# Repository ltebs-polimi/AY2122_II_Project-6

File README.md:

# Project 6: Respiration Monitoring in Sleep Positions

# Contents
[Introduction](#introduction)

[Hardware](#hardware)

[Firmware](#firmware)

[Data acquisition](#data-acquisition)

[Signal processing](#signal-processing)

[Machine learning model](#machine-learning-model)

[Repository structure](#repository-structure)

##

## Introduction
The aim of the project is to develop a system able to correctly classify four different sleep positions using an accelerometer. From the accelerometer we had to extract information about the respiration rate and, from these data, perform a classification with different machine learning algorithms.  

The steps of the project will be: 

- Development of a wearable device, where the accelerometer will be positioned on the chest of the subject;
- Data acquisition: following the specific protocol;
- Data processing (filtering and extraction of respiratory rate);
- Development of a Machine Learning algorithm to correctly classify the position of a subject from the signal. 

## Hardware
The components used to perform this project are: 

- PSoC
- 3-axis accelerometer (LIS3DH)
- Bluetooth module (HC-06)
- LEDs (red and blue)
- 9V battery
- Switch
- Voltage regulator (LM340T5)

To create the hardware of the system we first realized it on a breadboard and used the connections to design the printed circuit board (PCB). 

To do so, we realized the schematic and the board design on eagle, selecting the correct components to be used. Once the PCB design was done, we were able to produce the physical board with a process of acid etching, on which we soldered all the components. 

The switch allows to turn on and off the system without removing the battery. Initially there were a voltage divider to reduce the input voltage from 9V to 5V but was replaced with the voltage regulator due to the Bluetooth module not turning on.

To contain the PCB we designed in Solidworks a case which was then 3D printed. The initial idea was to apply the case to the chest of the subject to acquire the data, but this idea was then discarded due to the high encumbrance of the case.

The hardware is subdivided into two main parts: PCB and accelerometer. The PCB contain all the physical elements and their connections, while the accelerometer is stitched on a strap and is connected to the PCB through long cables. 

In this way, we apply the strap on the thorax of the subject, reducing the encumbrance and allowing a free movement of the accelerometer, and the case is kept near the acquisition site.

## Firmware
The accelerometer and the microprocessor communicate with a I2C Master/slave communication and the data are sent with a Bluetooth module. Then, there are two digital output to drive two LED. The first one (blue) turns ON when the accelerometer is sampling, the second one (red) turns ON if some error occurs in the communication with the accelerometer. 

When the device turns on, the microprocessor reads and writes the registers of the accelerometer.
We set the sampling frequency (CTRL\_REG1) at 50 Hz, the Full Scale Range (CTRL\_REG4) at +-2g and we enable the FIFO mode.   

The device is in the “waiting” status in which the accelerometer is not sampling and the FIFO register is empty. 

When the user sends a “start” signal, the device starts sampling for three minutes (according to the protocol for collecting the data), the blue light turns on and the data is saved in the FIFO register. 
When the register is full, we send the data with the Bluetooth module and reset the FIFO register. After three minutes the procedures stops and the device returns in the “waiting” status. 

If an error occurs during the sampling procedure, the sampling stops and the red LED turns on. It is possible to stop the sampling even with a “stop” signal. 

## Data acquisition
The protocol for the data acquisition consists in collecting data of 10 people in 4 different positions (supine, prone, lateral left, lateral right). Each subject must keep the position for 3 minutes. 

To make the procedure easier we implement a graphical interface in which the user can communicate with the device. 

The user has to choose a port and connect to it. The application allows also to rescan the port or disconnect to the port if needed. 

Then the user has to choose the position of the subject and starts the sampling. It is possible also to stop the sampling. 

After three minutes the data is saved as ‘.csv’ in a specific folder. The data are automatically saved and labelled and every sampling has its own file. It is possible to change the position of the subjects and start another sampling. 

The ‘.csv’ file contains all the data of the three axis and the position of the subject. These files will be then processed to obtain the information about the respiratory signal. 

## Signal processing

### Introduction
In order to process the data to extract the respiration signal and consequently the reparation rate, we have tried two different approaches, both based on data normalization and filtering data with Moving-average and Butterworth filters.

The main difference between these two methods regards the computation of the respiration rate:

- The first one compute the respiration rate based on pick coating function;
- The second one compute the respiration rate based on fast Fourier transform.

We decided to adopt the second approach, based on literature reviews.

### Explanation of the principal steps
The following are the main steps used in the algorithm:

1.  Z-TRANSFORM AND WINDOWING

In order to smooth and compare the data, a Z-normalization is applied. Based on a preliminary analysis of the raw-data plot, we choose only the horizontal component (X,Y axis) of the acceleration to extract the respiration signal, because the Z axis is most influenced by the tone sound vibration of the heart. 

Looking to the final aim of the ML analysis, we decide to divide any posture registration of 3 minutes in 3 windows of 60 seconds. In this way, from any registration of each posture, we obtain 3 signals of one minutes enlarging the dataset having 12 signals for each recorded volunteer (instead of 4).

The further analysis is applied to a 60 second window.

2. FILTERING

We have filtered transformed raw-data in 60 seconds window applying a cascade of filter:

- Moving-Average Filtering: to reduce the noise, we have applied a Moving average filter on a window of length corresponding to a maximal breathing rate (40 breaths/min).

|Average window size |(40/60) x Sampling Frequencies |
| :- | :- |

- Butterworth Filtering: the respiration frequencies in physiological condition can vary from 8 to 40 breaths for minutes (0.13-0.66 HZ). Therefore to extract the respiration signal we need to enhance this range of frequencies applying a Butterworth filter with parameters that are reported in the table. 

|FILTER ORDER|LOW F. (Hz)|HIGH F. (Hz)|
| :-: | :-: | :-: |
|4|0.05|0.66|

- BR selection: from the filtered signal we compute the Fast Fourier transform in order to make a frequency analysis. Subsequently, computing its power spectrum it is possible to select the breathing rate looking at the range of frequencies corresponding to physiological one (8-40 breath/min). This corresponds to the maximal in that range.

### Time and frequencies index extraction
In order to make further analysis on the signal, especially the classification purpose, we create a final dataset in which we report different time and frequencies domain index computed on the signal. (The list of index are reported in "index_computation.pdf" file, inside the "Data_collection" folder) 

After computed the principal index for ML analysis  reported in the table, we merge all the created dataset to proceed further.

## Machine learning model
For the classification we explored different ways. 

First, we tried to classify with the raw data coming from the accelerometer, we reached an accuracy of 100% mainly because of the orientation of the gravity acceleration that gives the major contribute to the signal.  

Once we have extracted the respiratory signal we tried to perform a multi-classification in two different ways:
- Using the entire respiratory signal, but this strategy did not perform very well, returning an accuracy of 35%. Analyzing the confusion matrix was evident that the relative positions were almos all misclassified;
- Using time and frequency indexes

### Data preparation
1. Univariate analysis: we removed the outlier to the variables that had a Gaussian distribution and we tried to normalize the other distributions. 

2. Multivariate analysis: we removed from the dataset the variables with high linear correlation and the variables which show a pattern in the bivariate distribution.

3. X and y dataset: after the standardization we split the dataset into y and x. The first one is the dataset containing the target (‘supine’, ‘prone’, ‘lateral R’, ‘lateral L’). The second one is the dataset containing the variables. We divided these datasets into train (70%) and test (30%). 

4. Machine Learning methods: we explored different ML methods. For each of them we selected the best parameters with a function, in order to perform the best classification. We explored:
   1. KNN (k-Nearest Neighbour)
   1. Decisional Tree
   1. Naïve-Bayes classifier
   1. Logistic regression
   1. Multi-layer Perceptron Classifier
   1. Linear support vector classifier
   1. Random Forest

We chose to use the linear SVM because it gave the most consistent results.
The classification performed over the four positions returned an accuracy of 63%, and by looking at the confusion matrix we understand that the prone and supine positions are often misclassified, probably because there is no significant difference between the respiratory signal in these situations.

To improve the classification we tried to merge the "supine" and "prone" positions, to obtain a classification over three classes instead of four. In this way we obtained an enhancement in both the f1 score and confusion matrix, resulting in a better classifier.

## Repository structure
- Folder "Bibliography" contains the papers used to determine how to perform signal processing and the optimal signal parameters to be used for the classification

- Folder "Data_collection" contains:

   - processed_data: the data processed to obtain the respiration signal

   - raw_data: the data coming from the accelerometer

   - GUI.py: the graphical interface for collecting the data

   - final_script: the script for the Machine Learning classification

   - index_computation: parameters of the signal used for the classification
   
   - processing.py: code to process the data and extract the respiratory features

   - total_proc_py: contains the dataframe used to classify the data

- Folder "Eagle" contains the PCB-related files

- Folder "Firmware" contains the PSOC design and workspace and all the files related to them 

- Folder "SolidWorks" contains the .SLDPRT and .SLDASM files of the 3D-printed case

- Folder "img" contains the images used for the README.md

- File "Hardware documentation" contains the information about the hardware and on how to correctly set it up

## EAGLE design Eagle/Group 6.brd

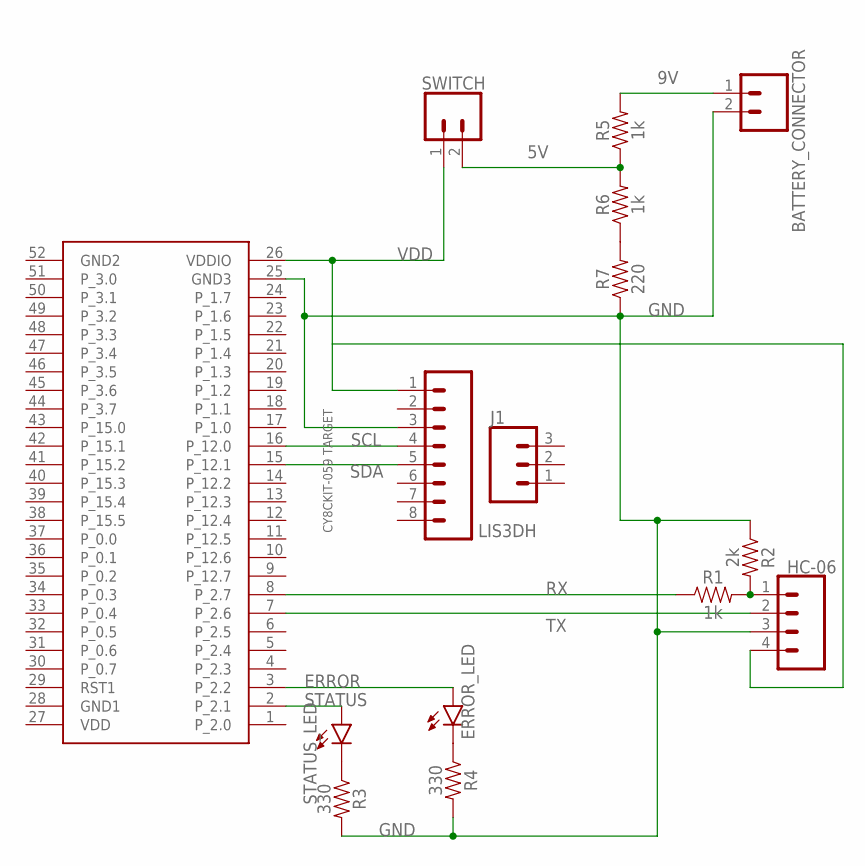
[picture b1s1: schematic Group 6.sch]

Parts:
BATTERY_CONNECTOR: CONN_02; 1X02
ERROR_LED: LED-3MM-NO_SILK; LED_3MM-NS
HC-06: CONN_04PTH; 1X04
J1: 455-1750-1-ND; 1X03
LIS3DH: CONN_08"; 1X08
R1, R5, R6: 1k; AXIAL-0.3
R2: 2k; AXIAL-0.3
R3, R4: 330; AXIAL-0.3
R7: 220; AXIAL-0.3
STATUS_LED: LED-3MM-NO_SILK; LED_3MM-NS
SWITCH: CONN_02; 1X02
U$1: CY8CKIT-059_TARGET_3

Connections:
5V: R5.P$1 (1), R6.P$2 (2), SWITCH.2
9V: BATTERY_CONNECTOR.1, R5.P$2 (2)
ERROR: ERROR_LED.A, U$1.3 (P_2.2)
GND: BATTERY_CONNECTOR.2, HC-06.3, LIS3DH.3, R2.P$1 (1), R3.P$2 (2), R4.P$2 (2), R7.P$1 (1), U$1.25 (GND3)
GND1: U$1.28 (GND1)
GND2: U$1.52 (GND2)
unnamed: ERROR_LED.K (C), R4.P$1 (1)
unnamed: R3.P$1 (1), STATUS_LED.K (C)
unnamed: HC-06.1, R1.P$2 (2), R2.P$2 (2)
unnamed: R6.P$1 (1), R7.P$2 (2)
RX: R1.P$1 (1), U$1.8 (P_2.7)
SCL: LIS3DH.4, U$1.16 (P_12.0)
SDA: LIS3DH.5, U$1.15 (P_12.1)
STATUS: STATUS_LED.A, U$1.2 (P_2.1)
TX: HC-06.2, U$1.7 (P_2.6)
VDD: HC-06.4, LIS3DH.1, SWITCH.1, U$1.26 (VDDIO), U$1.27 (VDD)

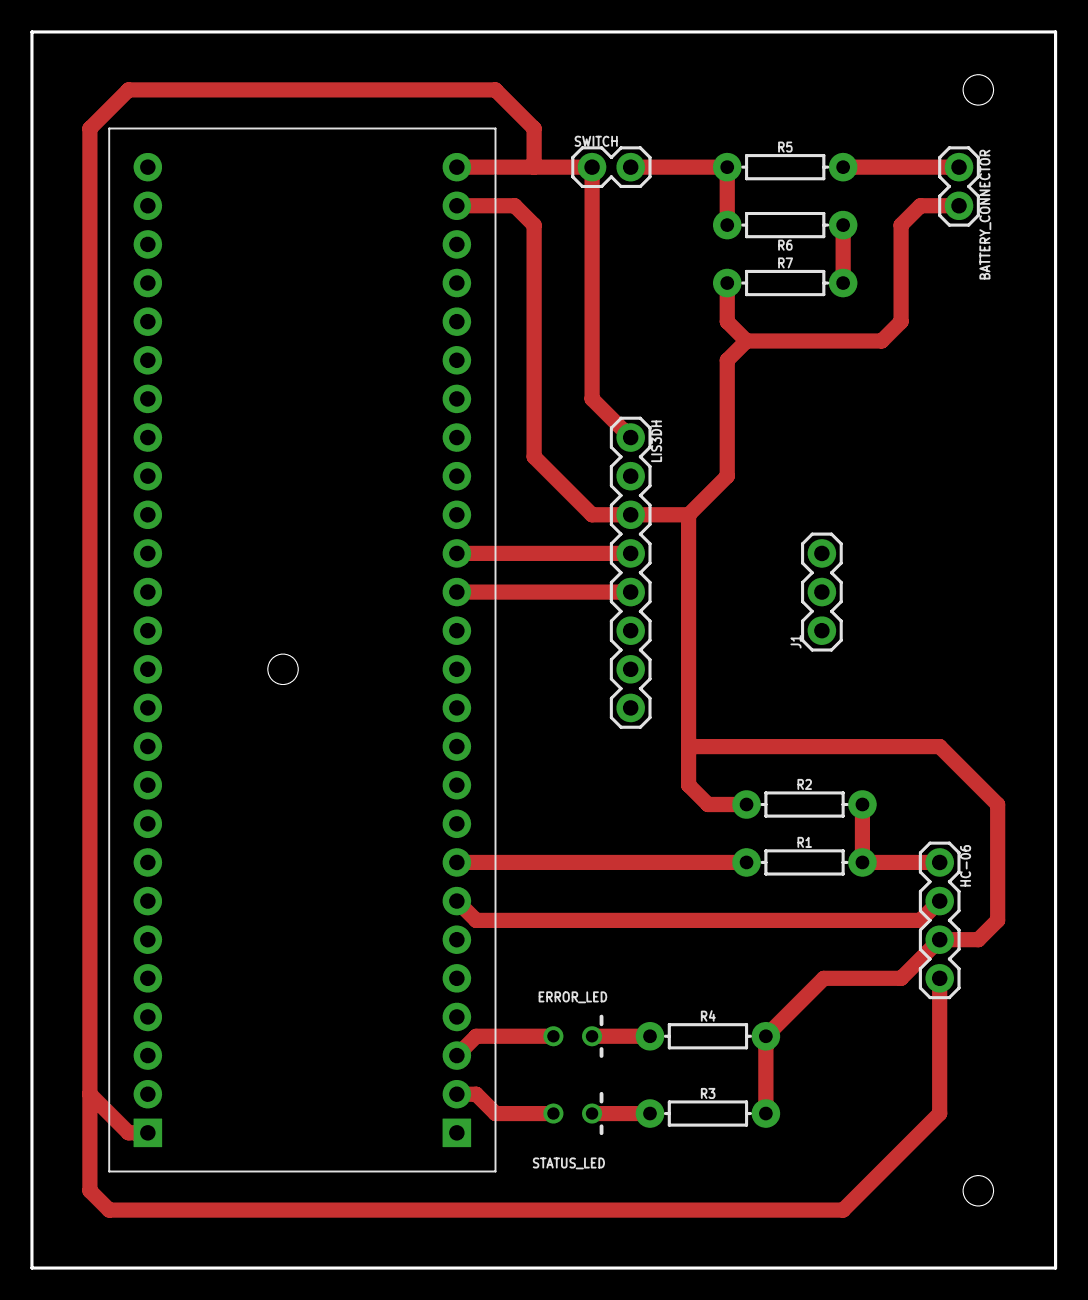
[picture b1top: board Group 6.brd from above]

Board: 2 copper layers, 67.3 x 81.3 mm, 15 parts (0 on the bottom side), 14 nets.

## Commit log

2022-05-09 Added base .gitignore
2022-06-24 Firmware
2022-07-07 Firmware-final delivery
2022-07-07 Graphical interface for data collection
2022-07-08 Raw data
2022-07-08 Processed data
2022-07-08 images for readme
2022-07-08 Created Eagle folder
2022-07-08 Added PCB files
2022-07-08 Created Solidworks folder
2022-07-08 Solidworks final delivery
2022-07-08 Uploaded hardware documentation
2022-07-08 Added missing images
2022-07-08 raw_data
2022-07-08 processed_data
2022-07-08 ML script
2022-07-08 HW documentation
2022-07-08 Added corrected ML script
2022-07-15 Uploaded final presentation

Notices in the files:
parts and their libraries:
SparkFun-Connectors: Licensing: Creative Commons ShareAlike 4.0 International - https://creativecommons.org/licenses/by-sa/4.0
